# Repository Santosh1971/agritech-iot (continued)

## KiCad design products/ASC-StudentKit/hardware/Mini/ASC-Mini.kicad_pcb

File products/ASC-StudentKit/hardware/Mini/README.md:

# ASC Mini rev A: schematic

The Mini carrier board for the ASC Student Kit. It is a half board, **97.4 × 47.0 mm**, held by **3 × M3** on the box's upper three bosses. Two Minis fit on one 100 × 100 mm panel (kit architecture §8).

## Status

| Item | State |
|---|---|
| Schematic | **First draft, generated.** 92 parts, 55 nets. `tools/check_design.py` and `tools/check_sheet.py` pass. **KiCad's ERC has not been run yet** (no KiCad 9 in the build container). Run it on the Mac first. |
| Pin map | Matches `../pinmap.json` (board `mini`), checked by `tools/check_design.py` |
| Footprints | 0402 resistors and small capacitors. J3 (the tester's pins) is a row of SMD pads on the back under the module, not fitted (DNP). The RTC cell holder is the flat Keystone 3034 on the back. 25 come from the KiCad 9.0.9 library. The HF46F relay footprint is our own (`ASC.pretty`), drawn from the Hongfa datasheet's PCB layout; check it against a real relay before ordering. The Grove socket uses a JST-PH 4-pin footprint as a stand-in; swap it for the HY2.0-4P part at layout. |
| PCB | **Routed, 2 layers, 1.6 mm.** 97.4 × 47.0 mm, 3 × M3. 1581 tracks (narrowest 0.15 mm), 287 vias (0.55 / 0.3 mm), clearance 0.15 mm. GND is joined by tracks as well as the pours on both layers. All checks below pass. **KiCad's zone fill and DRC have not been run yet** (no KiCad in the build container); run them on the Mac before ordering. |

## What is on it

| Block | Parts | Notes |
|---|---|---|
| 12 V input | J1 2-way 5.08 mm terminal, D1 SS34 (reverse polarity), D2 SMAJ26A (TVS), C1–C3 | **9–24 V in, 24 V maximum.** A terminal rather than a barrel jack, so the cable comes through a gland. |
| 12 V → 5 V | U2 TPS54202 buck (28 V max, 2 A), L1 10 µH, R1/R2 set **5.3 V**, D3 SS34 | The diode drop leaves about 5.0 V on +5V |
| USB-C | J2, R3/R4 5.1 k CC pull-downs, F1 0.5 A PTC, D4 SS34, U3 USBLC6-2SC6 ESD | Flashing and the console over native USB (GPIO19/20); also powers the board on a desk. D3 and D4 OR the two 5 V sources. |
| 5 V → 3.3 V | U4 AP7361C-33E (1 A LDO) | ESP32-S3 WiFi peaks of ≈350 mA, plus the RTC and the 3.3 V sensors |
| MCU | U1 ESP32-S3-MINI-1-**N8** | EN: R8/C14 plus a **RESET** button. GPIO0: R9 plus the **PAIR/BOOT** button. |
| Board ID | R10 30 k / R11 10 k = 0.25 × 3V3 on GPIO11 | The firmware reads this as "mini" |
| 12 V sense | R5 100 k / R6 10 k on GPIO10 | 24 V reads 2.18 V; 0 V means USB power only |
| RTC | U5 DS3231MZ+ (SOIC-8), BT1 CR2032 **on the back**, INT/SQW → GPIO16 | Internal I²C bus (GPIO12/13, 4.7 k pull-ups) |
| Sensor ports S1–S4 | J4–J7 JST-XH 4-pin: 1 GND · 2 3V3 · 3 5V · 4 SIG | SIG: 470 Ω in series, BAT54S clamps to 3V3 and GND, so a 5 V digital signal such as a flow sensor is safe. Port supplies fused: F2 0.5 A (5 V), F3 0.2 A (3V3). |
| I2C-1 student port | J8 Grove pinout: 1 SCL · 2 SDA · 3 3V3 · 4 GND | Its own bus (GPIO14/15), 4.7 k pull-ups |
| Relays OUT1/OUT2 | K1/K2 **Hongfa HF46F/005-HS1** (1 Form A, 5 A, 20.5 × 7.2 mm, 40 mA coil), Q2/Q3 AO3400A, D12/D13 flyback, J9/J10 2-way terminals (COM · NO) | GPIO35/36, gate pull-downs so the relays stay off through reset. Normally open only, which is all the rules use. **LOW VOLTAGE ONLY** on the silkscreen. |
| Buzzer | BZ1 5 V active 12 mm, Q1 AO3400A, D7 | GPIO46 is a strapping pin: R14 holds it low at reset |
| LEDs, seen through the clear lid | D5 **PWR**, D6 **STATUS** (GPIO48), D14 **OUT1**, D15 **OUT2** (on the relay coils, so they need no GPIO) | Each LED's name goes on the silkscreen (the `Silk` field on each part) |
| Test header | J3 1.27 mm × 8: 3V3, GND, EN, PAIR, D−, D+, TX, RX | The production tester's pogo pins, the same set as AWD1 |
| Mounting | H1–H3 M3 | Positions in `design.py` |

## Decided

- **Relays:** Hongfa HF46F (2026-10-08). It replaces the SRD and saves about 300 mm² of board.
- **Input:** 24 V maximum (2026-10-08). The TPS54202 (28 V) and the SMAJ26A suit that.
- **No OLED** in the kits (2026-10-08). The phone app is the screen, and the LEDs show through the clear lid.

## Please review

1. **Connector row.** The bottom edge has room for about 78 mm of connectors between the screw bosses. The three terminals (OUT1, OUT2, 12 V IN) need about 31 mm. The four XH ports and the Grove socket need about 58 mm more. Proposal: terminals along the bottom edge, and the XH and Grove sockets (vertical) in a second row just above them, with cables running down past the edge. USB-C goes on a side edge.
2. **HF46F footprint.** Print the footprint at 1:1 and push a real relay's pins through the paper before the first order.

## On the Mac, before ordering

1. Open `ASC-Mini.kicad_pro` in KiCad 9.
2. In the PCB editor press **B** to fill the zones (GND on both layers).
3. Run **Inspect → Design Rules Checker**. Expect nothing but silkscreen cosmetics. The USB-C footprint's own pads sit exactly 0.2 mm apart, which is fine under the 0.15 mm rule.
4. Check the HF46F relay footprint against a real relay (print 1:1).
5. Plot gerbers and drill files, or use the JLC plugin. Order 2 boards per 100 × 100 mm panel (architecture §8).

## Regenerate

```bash
cd products/ASC-StudentKit/hardware/Mini
python3 tools/gen_sch.py          # ASC-Mini.kicad_sch and tools/netlist.json
python3 tools/check_design.py     # pins vs pinmap.json, nets, power, strapping pins
python3 tools/check_sheet.py      # no accidental connections or overlaps on the sheet
python3 tools/gen_pcb.py          # ASC-Mini.kicad_pcb: outline, holes, placement, zones, labels (unrouted)
```

The board is routed by these steps. Freerouting 2.5.0 comes from Maven Central and needs Java 25:

```bash
export FREEROUTING_JAR=…/freerouting-2.5.0-executable.jar JAVA=…/java-25/bin/java
ROUTE_STAGE=signals POWER_W=0.45 SUPPLY_W=0.3 CLEARANCE=0.19 VIA_D=0.55 python3 tools/route.py   # every net but GND
python3 tools/patch_route.py                              # A* grid router with rip-up: whatever Freerouting left open
ROUTE_STAGE=gnd python3 tools/route.py                    # GND as tracks around the signals
PATCH_FINE=1 PATCH_CLR=0.16 python3 tools/patch_route.py GND
python3 tools/nudge_vias.py                               # move any via the grid left too close
```

Freerouting's result changes a lot with small inputs. The `ROUTE_TAG` and `ROUTE_ONLY` options run several variants side by side, so the best one can be imported. After a part moves, `tools/carry_routing.py OLD.kicad_pcb` keeps the existing routing except near the moved part, and `patch_route.py` reconnects the rest.

Checks, all passing on the committed board:

```bash
python3 tools/check_connect.py --include-gnd   # every net joined by copper (the module's GND pads are tied inside it)
python3 tools/check_clearance.py               # tracks, vias and pads of different nets ≥ 0.15 mm; edge; holes
python3 tools/check_board.py                   # pads clear of the edge and the screw heads
python3 tools/check_pour.py                    # GND is one piece; no dead pour patches or vias
```

`gen_sch.py` reads KiCad's symbol libraries from `KICAD_SYMBOL_DIR`. The default is KiCad 9 on macOS (`/Applications/KiCad/KiCad.app/Contents/SharedSupport/symbols`).

Then open `ASC-Mini.kicad_pro` in KiCad 9 and run **Inspect → Electrical Rules Checker**.

Edit `tools/design.py` and regenerate, rather than editing the schematic by hand, until the board layout starts. After that, switch to editing in KiCad, as AWD1 did.

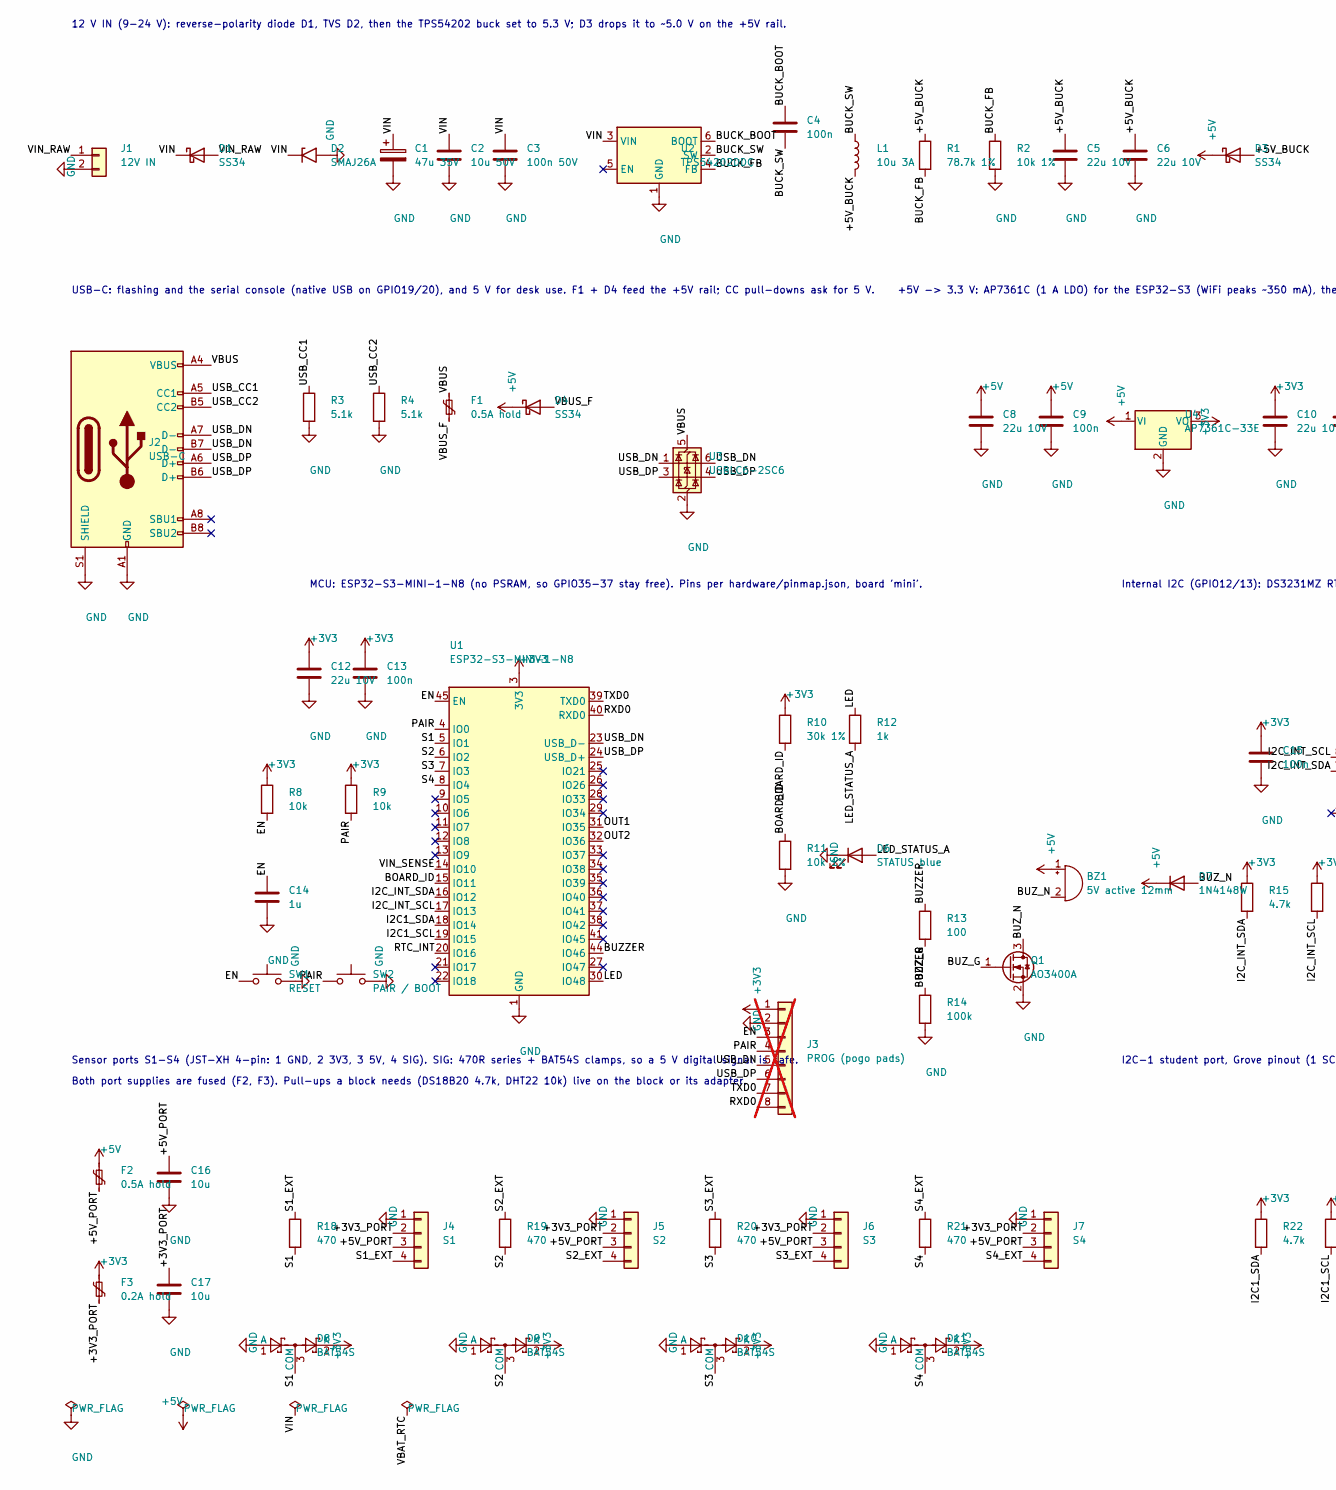
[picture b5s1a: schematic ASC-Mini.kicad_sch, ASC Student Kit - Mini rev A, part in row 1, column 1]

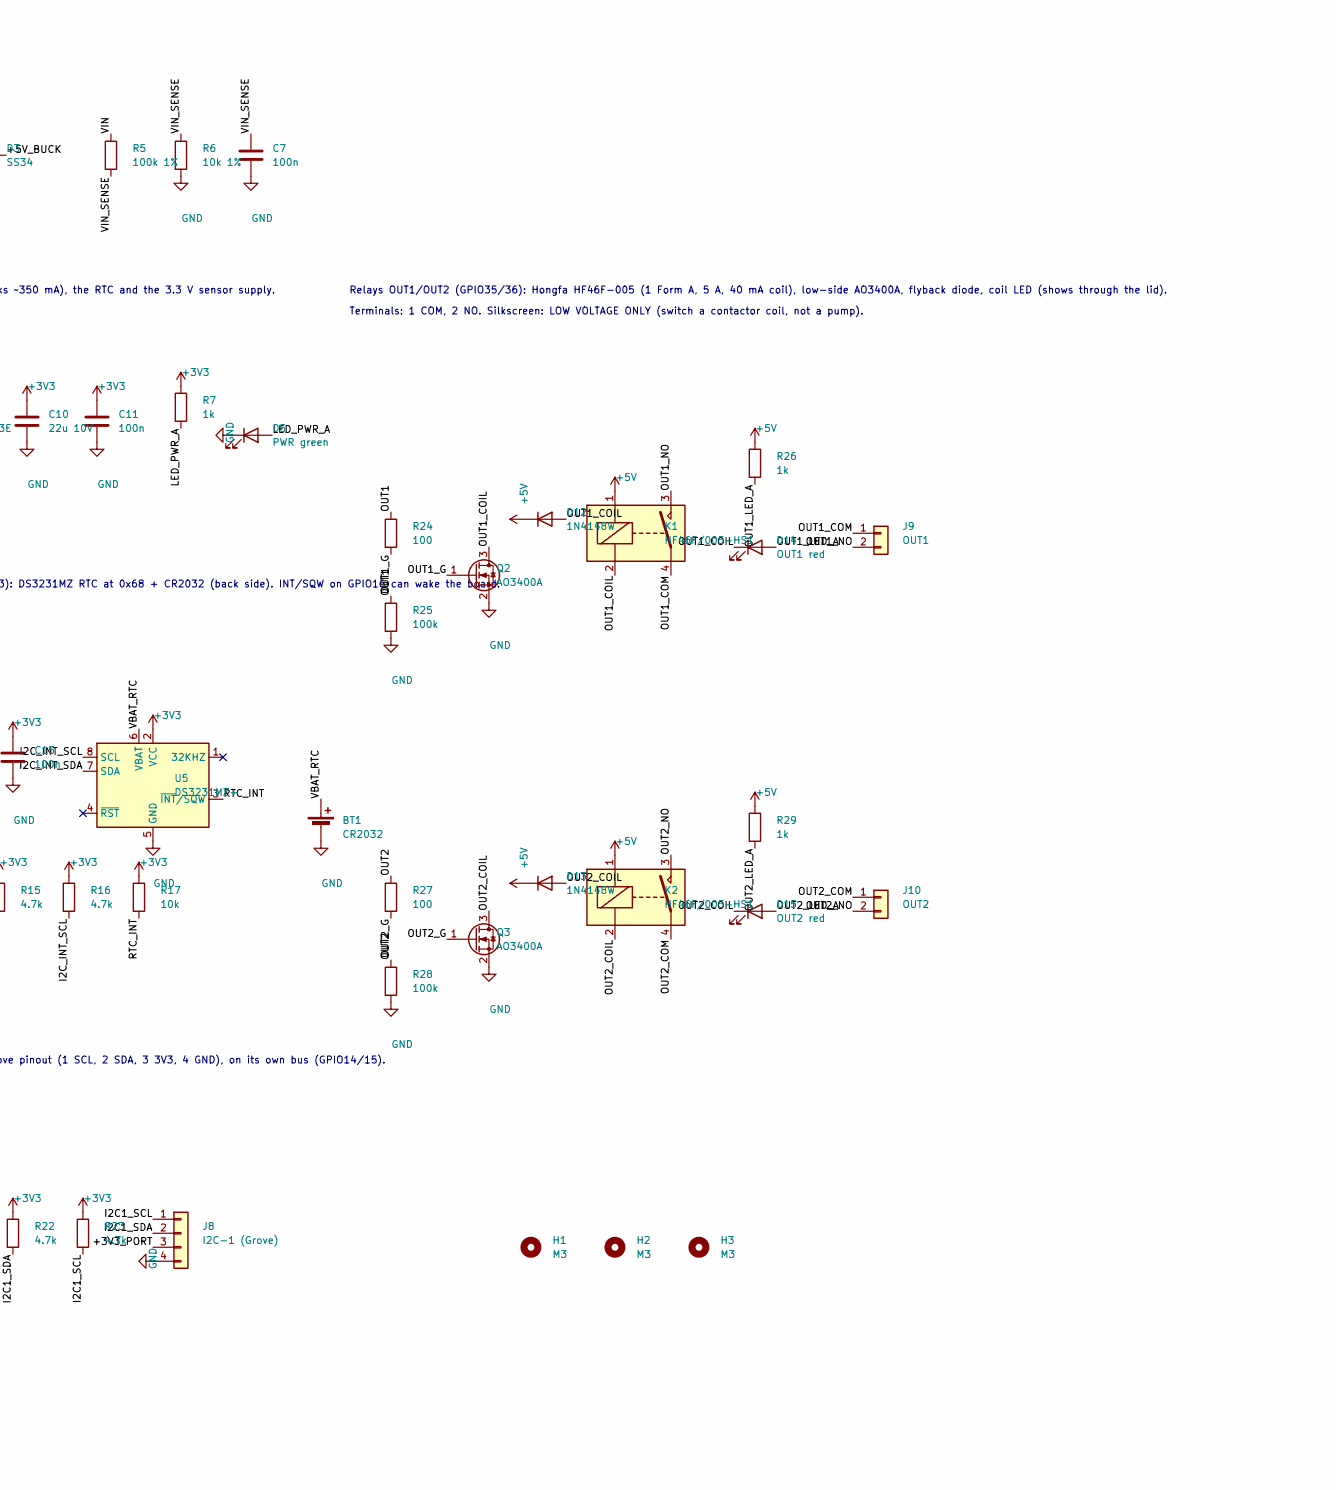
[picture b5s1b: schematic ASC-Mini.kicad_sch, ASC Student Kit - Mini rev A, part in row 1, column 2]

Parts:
BT1: CR2032; BatteryHolder_Keystone_3034_1x20mm
BZ1: 5V active 12mm; Buzzer_12x9.5RM7.6
C1: 47u 35V; CP_Elec_6.3x5.4
C2: 10u 50V; C_1206_3216Metric
C3: 100n 50V; C_0402_1005Metric
C4, C7, C9, C11, C13, C15: 100n; C_0402_1005Metric
C5, C6, C8, C10, C12: 22u 10V; C_1206_3216Metric
C14: 1u; C_0402_1005Metric
C16, C17: 10u; C_0805_2012Metric
D1, D3, D4: SS34; D_SMA
D2: SMAJ26A; D_SMA
D5: PWR green; LED_0805_2012Metric
D6: STATUS blue; LED_0805_2012Metric
D7, D12, D13: 1N4148W; D_SOD-123
D8, D9, D10, D11: BAT54S; SOT-23
D14: OUT1 red; LED_0805_2012Metric
D15: OUT2 red; LED_0805_2012Metric
F1, F2: 0.5A hold; Fuse_1206_3216Metric
F3: 0.2A hold; Fuse_1206_3216Metric
H1, H2, H3: M3; MountingHole_3.2mm_M3
J1: 12V IN; PhoenixContact_MSTBA_2,5_2-G-5,08_1x02_P5.08mm_Horizontal
J2: USB-C; USB_C_Receptacle_HRO_TYPE-C-31-M-12
J3: PROG (pogo pads); PinHeader_1x08_P1.27mm_Vertical_SMD_Pin1Left; not fitted
J4: S1; JST_XH_B4B-XH-A_1x04_P2.50mm_Vertical
J5: S2; JST_XH_B4B-XH-A_1x04_P2.50mm_Vertical
J6: S3; JST_XH_B4B-XH-A_1x04_P2.50mm_Vertical
J7: S4; JST_XH_B4B-XH-A_1x04_P2.50mm_Vertical
J8: I2C-1 (Grove); JST_PH_B4B-PH-K_1x04_P2.00mm_Vertical
J9: OUT1; PhoenixContact_MSTBA_2,5_2-G-5,08_1x02_P5.08mm_Horizontal
J10: OUT2; PhoenixContact_MSTBA_2,5_2-G-5,08_1x02_P5.08mm_Horizontal
K1, K2: HF46F/005-HS1; Relay_SPST_Hongfa_HF46F
L1: 10u 3A; L_6.3x6.3_H3
Q1, Q2, Q3: AO3400A; SOT-23
R1: 78.7k 1%; R_0402_1005Metric
R2, R6, R11: 10k 1%; R_0402_1005Metric
R3, R4: 5.1k; R_0402_1005Metric
R5: 100k 1%; R_0402_1005Metric
R7, R12, R26, R29: 1k; R_0402_1005Metric
R8, R9, R17: 10k; R_0402_1005Metric
R10: 30k 1%; R_0402_1005Metric
R13, R24, R27: 100; R_0402_1005Metric
R14, R25, R28: 100k; R_0402_1005Metric
R15, R16, R22, R23: 4.7k; R_0402_1005Metric
R18, R19, R20, R21: 470; R_0402_1005Metric
SW1: RESET; SW_SPST_TL3342
SW2: PAIR / BOOT; SW_SPST_TL3342
U1: ESP32-S3-MINI-1-N8; ESP32-S2-MINI-1
U2: TPS54202DDC; SOT-23-6
U3: USBLC6-2SC6; SOT-23-6
U4: AP7361C-33E; SOT-223-3_TabPin2
U5: DS3231MZ+; SOIC-8_3.9x4.9mm_P1.27mm

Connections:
+3V3: C10.1, C11.1, C12.1, C13.1, C15.1, D8.2 (K), D9.2 (K), D10.2 (K), D11.2 (K), F3.1, J3.1, R7.1, R8.1, R9.1, R10.1, R15.1, R16.1, R17.1, R22.1, R23.1, U1.3 (3V3), U4.3 (VO), U5.2 (VCC)
+5V: BZ1.1 (+), C8.1, C9.1, D3.1 (K), D4.1 (K), D7.1 (K), D12.1 (K), D13.1 (K), F2.1, K1.1, K2.1, R26.1, R29.1, U4.1 (VI)
/+3V3_PORT: C17.1, F3.2, J4.2, J5.2, J6.2, J7.2, J8.3
/+5V_BUCK: C5.1, C6.1, D3.2 (A), L1.2, R1.1
/+5V_PORT: C16.1, F2.2, J4.3, J5.3, J6.3, J7.3
/BOARD_ID: R10.2, R11.1, U1.15 (IO11)
/BUCK_BOOT: C4.1, U2.6 (BOOT)
/BUCK_FB: R1.2, R2.1, U2.4 (FB)
/BUCK_SW: C4.2, L1.1, U2.2 (SW)
/BUZZER: R13.1, R14.1, U1.44 (IO46)
/BUZ_G: Q1.1 (G), R13.2
/BUZ_N: BZ1.2 (-), D7.2 (A), Q1.3 (D)
/EN: C14.1, J3.3, R8.2, SW1.1, U1.45 (EN)
/I2C1_SCL: J8.1, R23.2, U1.19 (IO15)
/I2C1_SDA: J8.2, R22.2, U1.18 (IO14)
/I2C_INT_SCL: R16.2, U1.17 (IO13), U5.8 (SCL)
/I2C_INT_SDA: R15.2, U1.16 (IO12), U5.7 (SDA)
/LED: R12.1, U1.30 (IO48)
/LED_PWR_A: D5.2 (A), R7.2
/LED_STATUS_A: D6.2 (A), R12.2
/OUT1: R24.1, R25.1, U1.31 (IO35)
/OUT1_COIL: D12.2 (A), D14.1 (K), K1.2, Q2.3 (D)
/OUT1_COM: J9.1, K1.4
/OUT1_G: Q2.1 (G), R24.2
/OUT1_LED_A: D14.2 (A), R26.2
/OUT1_NO: J9.2, K1.3
/OUT2: R27.1, R28.1, U1.32 (IO36)
/OUT2_COIL: D13.2 (A), D15.1 (K), K2.2, Q3.3 (D)
/OUT2_COM: J10.1, K2.4
/OUT2_G: Q3.1 (G), R27.2
/OUT2_LED_A: D15.2 (A), R29.2
/OUT2_NO: J10.2, K2.3
/PAIR: J3.4, R9.2, SW2.1, U1.4 (IO0)
/RTC_INT: R17.2, U1.20 (IO16), U5.3 (~INT/SQW)
/RXD0: J3.8, U1.40 (RXD0)
/S1: D8.3 (COM), R18.2, U1.5 (IO1)
/S1_EXT: J4.4, R18.1
/S2: D9.3 (COM), R19.2, U1.6 (IO2)
/S2_EXT: J5.4, R19.1
/S3: D10.3 (COM), R20.2, U1.7 (IO3)
/S3_EXT: J6.4, R20.1
/S4: D11.3 (COM), R21.2, U1.8 (IO4)
/S4_EXT: J7.4, R21.1
/TXD0: J3.7, U1.39 (TXD0)
/USB_CC1: J2.A5 (CC1), R3.1
/USB_CC2: J2.B5 (CC2), R4.1
/USB_DN: J2.A7 (D-), J2.B7 (D-), J3.5, U1.23 (USB_D-), U3.1 (I/O1), U3.6 (I/O1)
/USB_DP: J2.A6 (D+), J2.B6 (D+), J3.6, U1.24 (USB_D+), U3.3 (I/O2), U3.4 (I/O2)
/VBAT_RTC: BT1.1 (+), U5.6 (VBAT)
/VBUS: F1.1, J2.A4 (VBUS), J2.A9 (VBUS), J2.B4 (VBUS), J2.B9 (VBUS), U3.5 (VBUS)
/VBUS_F: D4.2 (A), F1.2
/VIN: C1.1, C2.1, C3.1, D1.1 (K), D2.1 (A1), R5.1, U2.3 (VIN)
/VIN_RAW: D1.2 (A), J1.1
/VIN_SENSE: C7.1, R5.2, R6.1, U1.14 (IO10)
GND: BT1.2 (-), C1.2, C2.2, C3.2, C5.2, C6.2, C7.2, C8.2, C9.2, C10.2, C11.2, C12.2, C13.2, C14.2, C15.2, C16.2, C17.2, D2.2 (A2), D5.1 (K), D6.1 (K), D8.1 (A), D9.1 (A), D10.1 (A), D11.1 (A), J1.2, J2.A1 (GND), J2.A12 (GND), J2.B1 (GND), J2.B12 (GND), J2.S1 (SHIELD), J3.2, J4.1, J5.1, J6.1, J7.1, J8.4, Q1.2 (S), Q2.2 (S), Q3.2 (S), R2.2, R3.2, R4.2, R6.2, R11.2, R14.2, R25.2, R28.2, SW1.2, SW2.2, U1.1 (GND), U1.2 (GND), U1.42 (GND), U1.43 (GND), U1.46 (GND), U1.47 (GND), U1.48 (GND), U1.49 (GND), U1.50 (GND), U1.51 (GND), U1.52 (GND), U1.53 (GND), U1.54 (GND), U1.55 (GND), U1.56 (GND), U1.57 (GND), U1.58 (GND), U1.59 (GND), U1.60 (GND), U1.61 (GND), U1.62 (GND), U1.63 (GND), U1.64 (GND), U1.65 (GND), U2.1 (GND), U3.2 (GND), U4.2 (GND), U5.5 (GND)

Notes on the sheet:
12 V IN (9-24 V): reverse-polarity diode D1, TVS D2, then the TPS54202 buck set to 5.3 V; D3 drops it to ~5.0 V on the +5V rail.
USB-C: flashing and the serial console (native USB on GPIO19/20), and 5 V for desk use. F1 + D4 feed the +5V rail; CC pull-downs ask for 5 V.
+5V -> 3.3 V: AP7361C (1 A LDO) for the ESP32-S3 (WiFi peaks ~350 mA), the RTC and the 3.3 V sensor supply.
MCU: ESP32-S3-MINI-1-N8 (no PSRAM, so GPIO35-37 stay free). Pins per hardware/pinmap.json, board 'mini'.
Internal I2C (GPIO12/13): DS3231MZ RTC at 0x68 + CR2032 (back side). INT/SQW on GPIO16 can wake the board.
Sensor ports S1-S4 (JST-XH 4-pin: 1 GND, 2 3V3, 3 5V, 4 SIG). SIG: 470R series + BAT54S clamps, so a 5 V digital signal is safe.
Both port supplies are fused (F2, F3). Pull-ups a block needs (DS18B20 4.7k, DHT22 10k) live on the block or its adapter.
I2C-1 student port, Grove pinout (1 SCL, 2 SDA, 3 3V3, 4 GND), on its own bus (GPIO14/15).
Relays OUT1/OUT2 (GPIO35/36): Hongfa HF46F-005 (1 Form A, 5 A, 40 mA coil), low-side AO3400A, flyback diode, coil LED (shows through the lid).
Terminals: 1 COM, 2 NO. Silkscreen: LOW VOLTAGE ONLY (switch a contactor coil, not a pump).

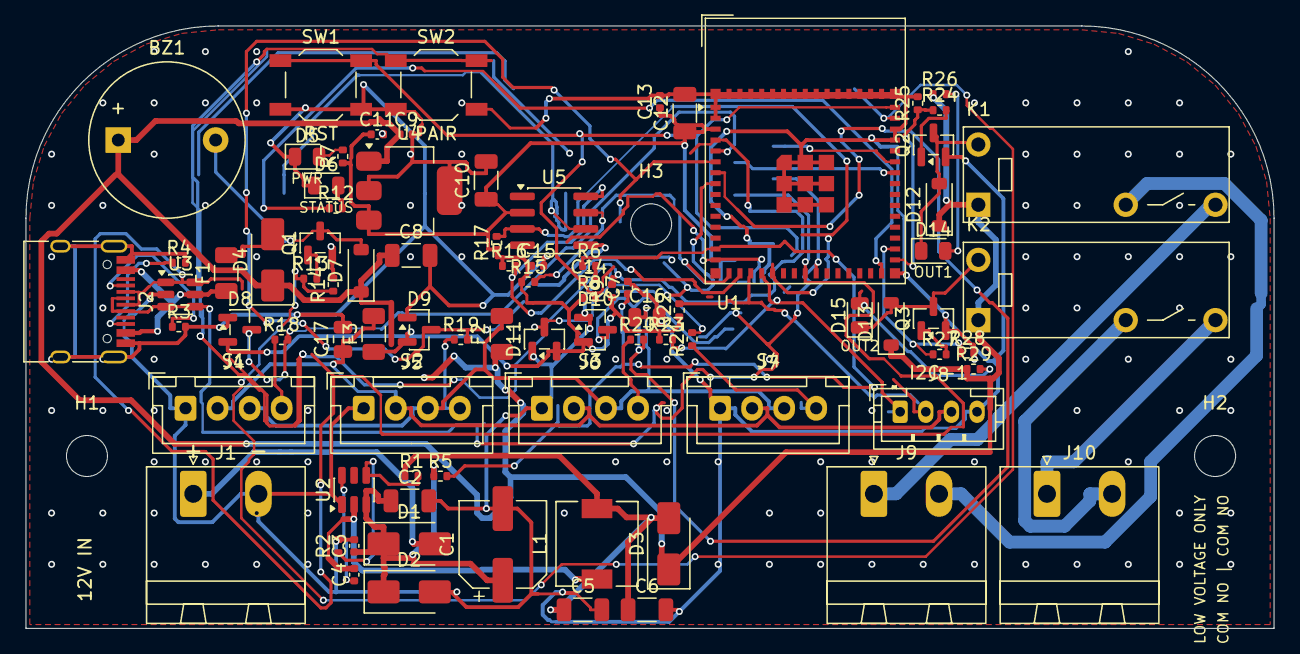
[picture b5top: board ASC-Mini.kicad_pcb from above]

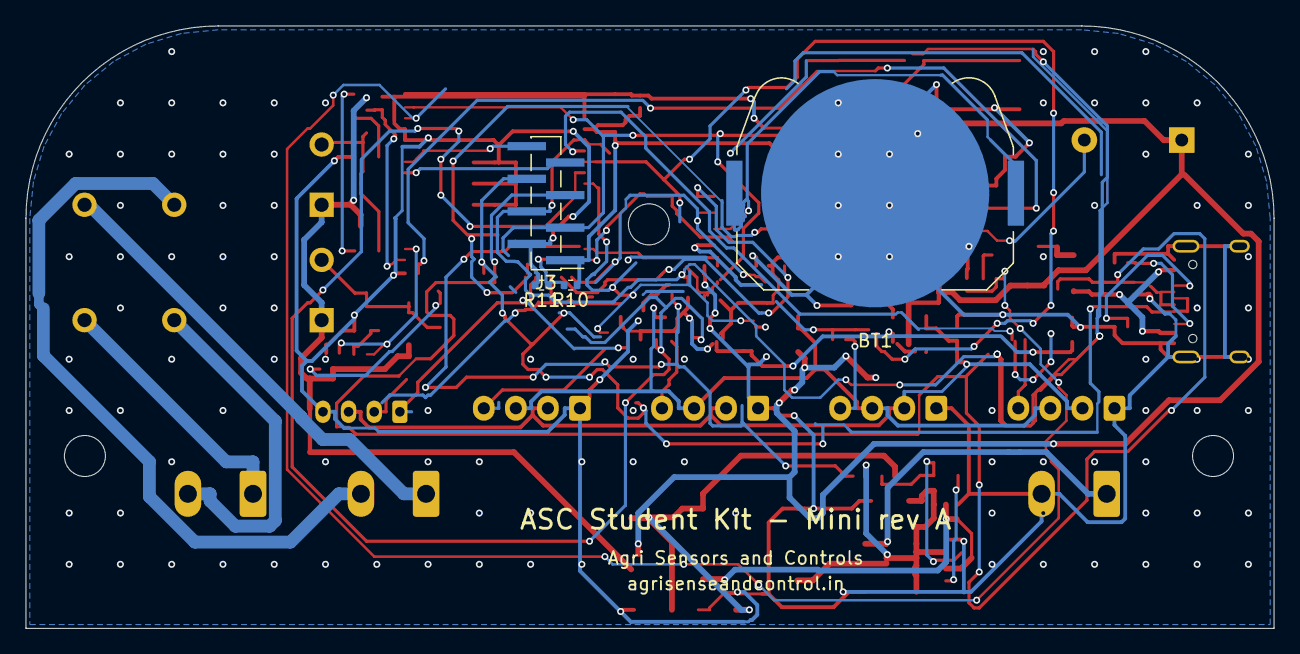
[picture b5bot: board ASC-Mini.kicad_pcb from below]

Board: 2 copper layers, 97.4 x 47.0 mm, 92 parts (4 on the bottom side), 55 nets.

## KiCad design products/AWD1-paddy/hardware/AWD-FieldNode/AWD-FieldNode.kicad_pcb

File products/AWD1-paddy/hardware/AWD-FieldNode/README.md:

# AWD field node v0.1: segmented capacitive level strip

This board is the paddy AWD (alternate wetting and drying) field node. It is a T-shaped, 4-layer PCB.

- **Head:** 40 × 60 mm, inside a sealed 50 mm PVC end cap. It carries an ESP32-S3-MINI-1, an ISC-SX1262-B LoRa module (the same module and pin map as WPC), a LiFePO4 14500 cell and an SMA connector.
- **Strip:** 10 × 300 mm, pushed into the AWD tube.
  - 12 sensing pads, 8 × 18 mm on a 20 mm pitch, covering +7 to −17 cm.
  - One dry reference pad.
  - One GND water-return pad.

The node reports to a WPC-style Master over LoRa at 866 MHz.

## Status

| Item | State |
|---|---|
| Schematic | **v0.2 (2026-10-11): field charging added**, the same block as TH2 (see *v0.2 power* below). 66 parts, ERC reports 0 violations. |
| PCB ↔ schematic | **Out of date since v0.2.** The 51 existing footprints are still linked: `gen_sch.py` now keeps symbol UUIDs. The 15 new parts (U3, U4, U5, F1, J4, D2, D3, R8–R13, C8, C9) must be added with *Update PCB from Schematic*, then placed and routed on the head. TP1 is renamed from T14 to VBUS_DET. |
| Outline, stack-up, zones | Done. Board is 4 layers: F pads / In1 GND (hatched 25 % under the pads) / In2 sense lanes + GND / B GND. |
| Strip routing | **Done.** Each pad → via → In2.Cu lane (0.15 mm, 0.6 mm pitch) → 45° fan-out → RS series resistor. |
| Head placement | Placed next to the pins each part serves. J3 (battery JST) is on the back, under the SX1262. |
| Head routing | **Done** by Freerouting 1.9.0 (passes in `route/`) on F.Cu and In2.Cu, with GND stitching vias added by `tools/stitch.py`. Hand-routed nets: R4's +3V3 (via → B.Cu → J2 pin 1); the SX1262 VDD feed (B.Cu at x = 107.4 mm), which clears the straight 50 Ω antenna line. |
| Remaining DRC | **U1 pad 63** (an ESP32 corner GND pad) sits in a small F.Cu GND island. The touch fan-out fills that corner, so no via fits. It is harmless because the module ties its GND pads together internally. **J1** is an edge-launch SMA and touches the edge on purpose; check its seating against the Amphenol 132289 datasheet. The rest are silkscreen cosmetics and three single-spoke thermals. |

## Pin map (ESP32-S3)

| Function | GPIO |
|---|---|
| Touch T1–T12 → pads P1–P12 | IO1–IO12 |
| Touch T13 → REF pad | IO13 |
| VBUS_DET (charger present, deep-sleep wake), to TP1 | IO14 |
| VBAT_ADC (ADC2_CH4) / VBAT_EN | IO15 / IO16 |
| LoRa DIO1 / BUSY / RST | IO17 / IO18 / IO21 |
| LoRa NSS / SCK / MOSI / MISO | IO39 / IO40 / IO41 / IO42 |
| LED | IO38 |
| PAIR/BOOT button | IO0 |
| USB D−/D+ and UART0 | J2 (1.27 mm pogo/header) |

## v0.2 power: charging in the field through a magnetic socket

v0.1 put the 14500 straight onto the 3V3 rail with no charger, so the box had to be opened to charge the cell. v0.2 adds the same charging block as TH2:

```
J4 magnetic socket (VBUS, D-, D+, GND) -> F1 0.5 A polyfuse -> VBUS -> U3 CN3058E (0.31 A, 3.6 V CV) -> VBAT
J3 14500 -> Q1 reverse protection -> VBAT -> U4 RT9080-33 (2 uA Iq) -> +3V3
```

- **The LDO is now required:** while charging, VBAT sits at 3.6 V, which is the ESP32-S3's absolute maximum.
- **Battery sense:** R4 now measures **VBAT** (before the LDO), not +3V3.
- **USB:** J4's D−/D+ join the native-USB lines already on J2, through U5 (USBLC6 ESD protection). The node can be flashed through the magnetic cable without opening the box.
- **Charge LEDs:** D2 red (charging) and D3 green (full) run off VBUS. Place them under, or next to, the front-shell light window.
- **Charger detect:** VBUS_DET (R12/R13 divider to IO14, an RTC GPIO) wakes the S3 when the cable is clipped on.
- **Enclosure:** the magnetic socket needs its own wall hole, because the side hole is used by the SMA. That waits until the socket's flange size is known (ElectronifyIndia 4-pin flanged for prototypes, HytePro M826 waterproof for production). It goes in the shared AWD/TH shell.

## AWD thresholds

| Action | Condition |
|---|---|
| Pump OFF (+5 cm) | P2 wet |
| Pump ON (−15 cm) | P11 dry |
| SOIL line (0 cm) | Printed on both faces as the installation depth mark |

## Regenerate

The files are generated from `tools/design.py`, which defines the parts, nets and geometry.

```bash
cd products/AWD1-paddy/hardware/AWD-FieldNode
python3 tools/gen_sch.py      # schematic, AWD.kicad_sym, tools/netlist.json
python3 tools/gen_fp.py       # AWD.pretty pad footprints
/Applications/KiCad/KiCad.app/Contents/Frameworks/Python.framework/Versions/Current/bin/python3 tools/gen_pcb.py
```

**Warning:** `gen_pcb.py` rebuilds the board from scratch and **throws away the head routing**. Never run it again. `gen_sch.py` is safe: since v0.2 it reuses the existing schematic's root and symbol UUIDs, so the routed PCB stays linked. After a regenerate, run *Update PCB from Schematic* in KiCad to pull in new parts.

### Re-routing the head and watching it

To watch the autorouter work:

1. Unlock the strip tracks if you need to move them; leave them locked otherwise.
2. Remove the `GND_top_head` and `GND_in2` zones.
3. Run *File → Export → Specctra DSN*.
4. In the `.dsn` file, change `In1.Cu` (and optionally `B.Cu`) to `(type power)`.
5. Run:

```bash
java -jar ~/Applications/freerouting/freerouting-1.9.0.jar -de route/AWD-FieldNode.dsn
```

6. Press **Autorouter** in the Freerouting window to watch it route.
7. Save the session, then run *File → Import → Specctra Session* in KiCad.
8. Refill the zones (B).

## Fab notes

- **Order with JLCPCB stack-up JLC04161H-7628** (L1–L2 prepreg 0.21 mm, εr ≈ 4.4). The antenna feed (`/RF_ANT`, SX1262 pad 1 → J1) is a straight 10.9 mm, 0.36 mm trace on F.Cu over the In1 GND plane: about 50 Ω. `AWD-FieldNode.kicad_dru` keeps the F.Cu pour 0.5 mm away from it. To hold ±10 %, tick impedance control.
- `fab/` holds gerbers + drills (`AWD-FieldNode-gerbers.zip`), BOM and CPL. These were exported with kicad-cli; regenerate them after any board change.

- 4 layers, 1.6 mm FR4, ENIG finish, solder mask on both sides, vias tented.
- The pads have **no mask opening**. Below the neck the strip carries no exposed copper.
- After assembly, dip-coat the strip in 2-part epoxy or PU, 100–200 µm thick, and seal the routed edges.

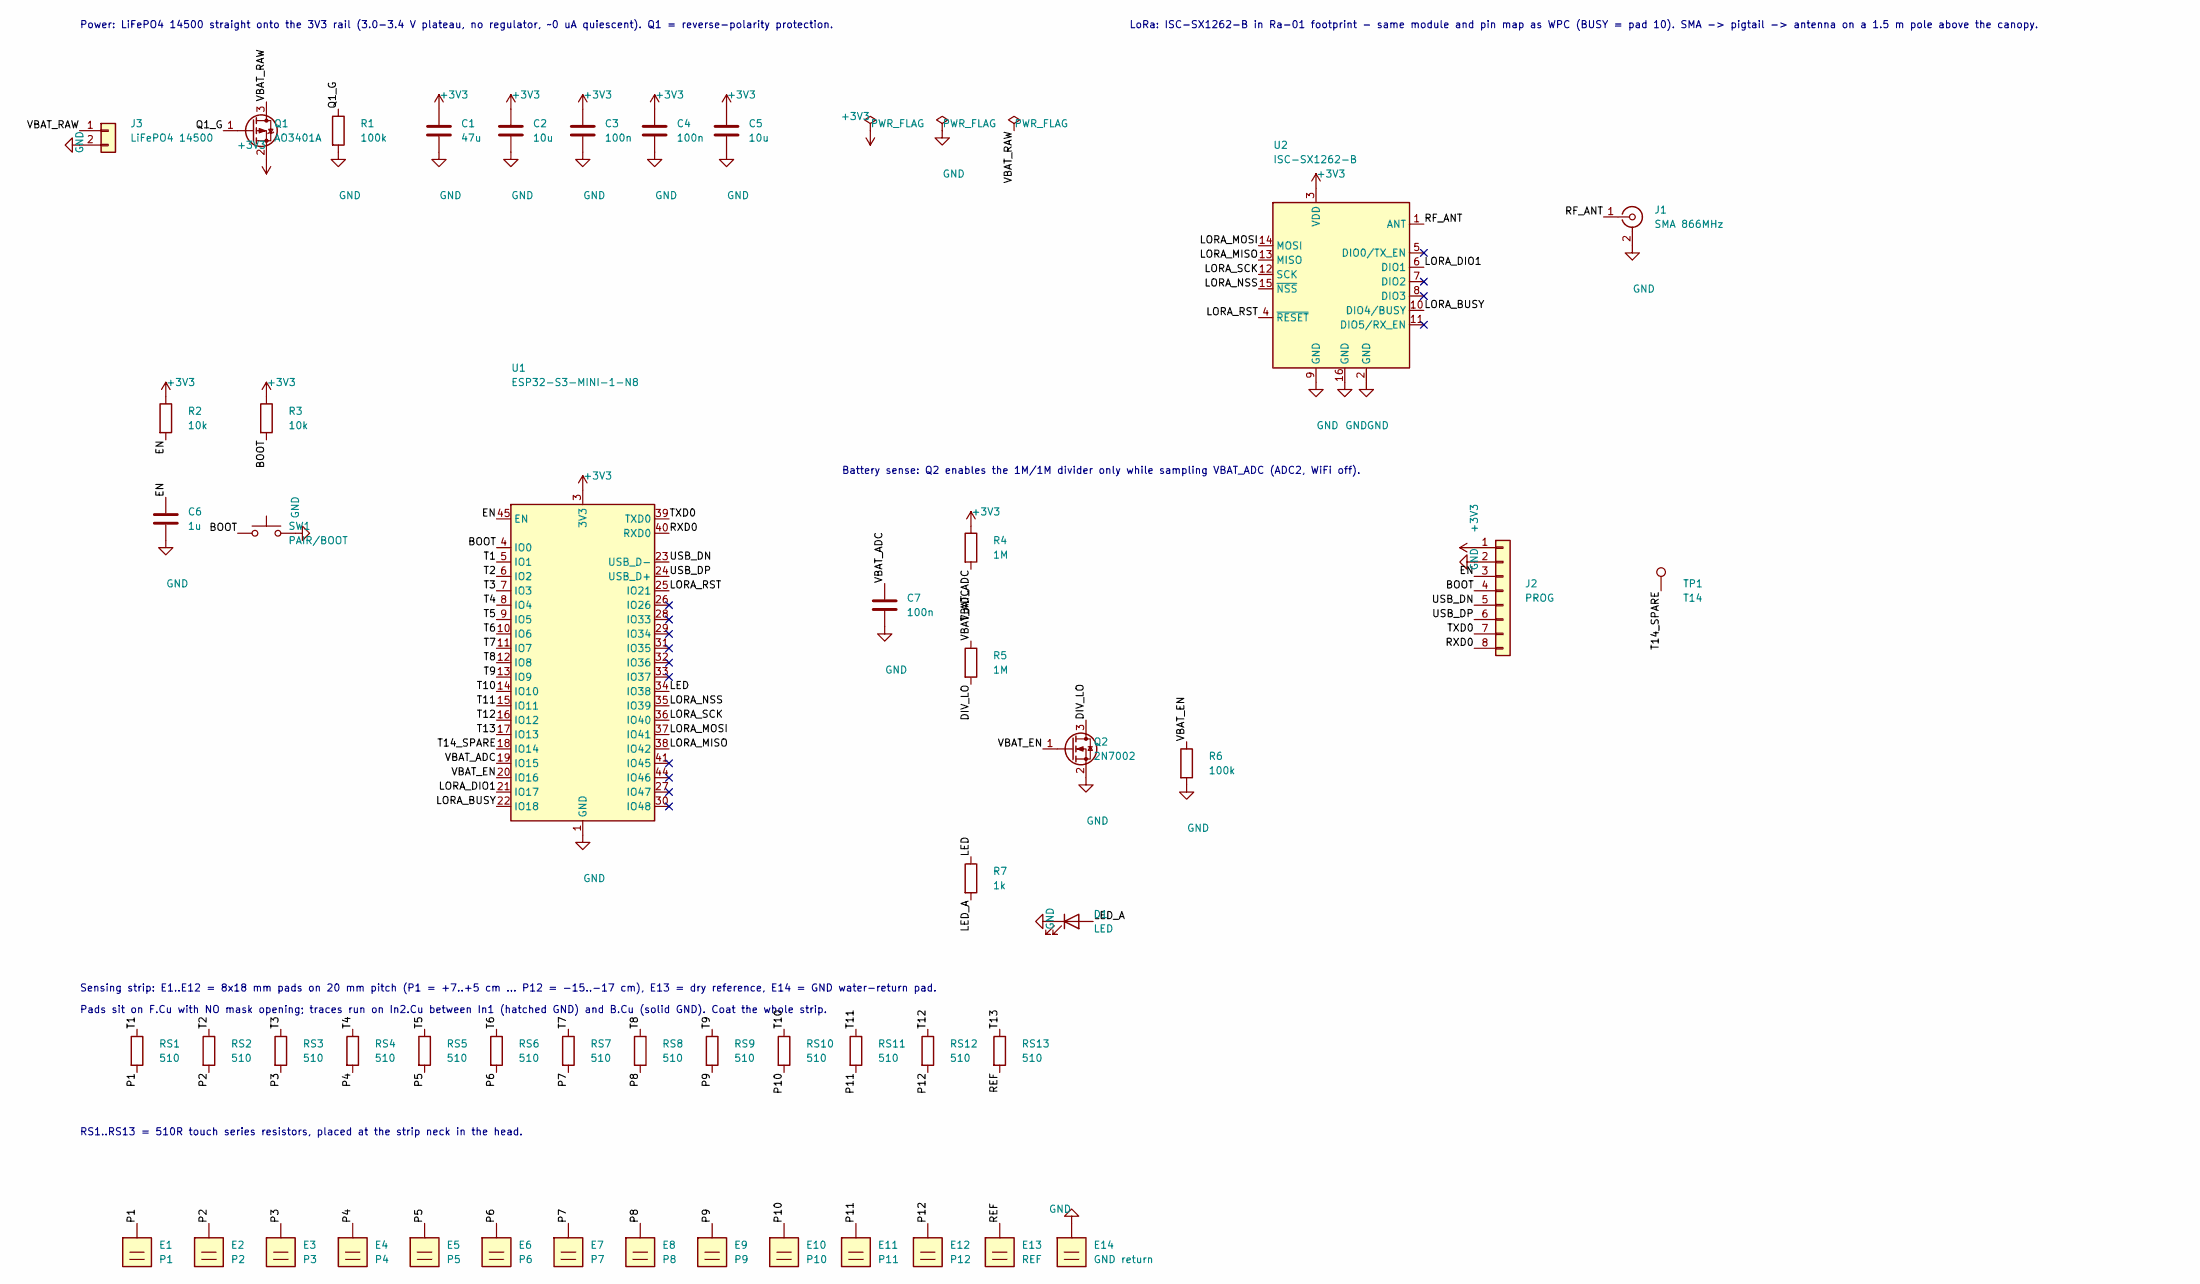
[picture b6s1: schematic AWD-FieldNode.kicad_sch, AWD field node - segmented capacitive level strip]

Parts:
C1: 47u; C_1206_3216Metric
C2, C5: 10u; C_0805_2012Metric
C3, C4, C7: 100n; C_0603_1608Metric
C6: 1u; C_0603_1608Metric
D1: LED; LED_0603_1608Metric
E1: P1; SensePad_8x18mm
E2: P2; SensePad_8x18mm
E3: P3; SensePad_8x18mm
E4: P4; SensePad_8x18mm
E5: P5; SensePad_8x18mm
E6: P6; SensePad_8x18mm
E7: P7; SensePad_8x18mm
E8: P8; SensePad_8x18mm
E9: P9; SensePad_8x18mm
E10: P10; SensePad_8x18mm
E11: P11; SensePad_8x18mm
E12: P12; SensePad_8x18mm
E13: REF; SensePad_8x12mm
E14: GND return; ReturnPad_8x20mm
J1: SMA 866MHz; SMA_Amphenol_132289_EdgeMount
J2: PROG; PinHeader_1x08_P1.27mm_Vertical
J3: LiFePO4 14500; JST_PH_S2B-PH-SM4-TB_1x02-1MP_P2.00mm_Horizontal
Q1: AO3401A; SOT-23
Q2: 2N7002; SOT-23
R1, R6: 100k; R_0603_1608Metric
R2, R3: 10k; R_0603_1608Metric
R4, R5: 1M; R_0603_1608Metric
R7: 1k; R_0603_1608Metric
RS1, RS2, RS3, RS4, RS5, RS6, RS7, RS8, RS9, RS10, RS11, RS12, RS13: 510; R_0402_1005Metric
SW1: PAIR/BOOT; SW_SPST_TL3342
TP1: T14; TestPoint_Pad_D1.5mm
U1: ESP32-S3-MINI-1-N8; ESP32-S2-MINI-1
U2: ISC-SX1262-B; Ai-Thinker-Ra-01-LoRa

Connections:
+3V3: C1.1, C2.1, C3.1, C4.1, C5.1, J2.1, Q1.2 (S), R2.1, R3.1, R4.1, U1.3 (3V3), U2.3 (VDD)
/BOOT: J2.4, R3.2, SW1.1, U1.4 (IO0)
/DIV_LO: Q2.3 (D), R5.2
/EN: C6.1, J2.3, R2.2, U1.45 (EN)
/LED: R7.1, U1.34 (IO38)
/LED_A: D1.2 (A), R7.2
/LORA_BUSY: U1.22 (IO18), U2.10 (DIO4/BUSY)
/LORA_DIO1: U1.21 (IO17), U2.6 (DIO1)
/LORA_MISO: U1.38 (IO42), U2.13 (MISO)
/LORA_MOSI: U1.37 (IO41), U2.14 (MOSI)
/LORA_NSS: U1.35 (IO39), U2.15 (~NSS)
/LORA_RST: U1.25 (IO21), U2.4 (~RESET)
/LORA_SCK: U1.36 (IO40), U2.12 (SCK)
/P1: E1.1, RS1.2
/P2: E2.1, RS2.2
/P3: E3.1, RS3.2
/P4: E4.1, RS4.2
/P5: E5.1, RS5.2
/P6: E6.1, RS6.2
/P7: E7.1, RS7.2
/P8: E8.1, RS8.2
/P9: E9.1, RS9.2
/P10: E10.1, RS10.2
/P11: E11.1, RS11.2
/P12: E12.1, RS12.2
/Q1_G: Q1.1 (G), R1.1
/REF: E13.1, RS13.2
/RF_ANT: J1.1 (In), U2.1 (ANT)
/RXD0: J2.8, U1.40 (RXD0)
/T1: RS1.1, U1.5 (IO1)
/T2: RS2.1, U1.6 (IO2)
/T3: RS3.1, U1.7 (IO3)
/T4: RS4.1, U1.8 (IO4)
/T5: RS5.1, U1.9 (IO5)
/T6: RS6.1, U1.10 (IO6)
/T7: RS7.1, U1.11 (IO7)
/T8: RS8.1, U1.12 (IO8)
/T9: RS9.1, U1.13 (IO9)
/T10: RS10.1, U1.14 (IO10)
/T11: RS11.1, U1.15 (IO11)
/T12: RS12.1, U1.16 (IO12)
/T13: RS13.1, U1.17 (IO13)
/T14_SPARE: TP1.1, U1.18 (IO14)
/TXD0: J2.7, U1.39 (TXD0)
/USB_DN: J2.5, U1.23 (USB_D-)
/USB_DP: J2.6, U1.24 (USB_D+)
/VBAT_ADC: C7.1, R4.2, R5.1, U1.19 (IO15)
/VBAT_EN: Q2.1 (G), R6.1, U1.20 (IO16)
/VBAT_RAW: J3.1, Q1.3 (D)
GND: C1.2, C2.2, C3.2, C4.2, C5.2, C6.2, C7.2, D1.1 (K), E14.1, J1.2 (Ext), J2.2, J3.2, Q2.2 (S), R1.2, R6.2, SW1.2, U1.1 (GND), U1.2 (GND), U1.42 (GND), U1.43 (GND), U1.46 (GND), U1.47 (GND), U1.48 (GND), U1.49 (GND), U1.50 (GND), U1.51 (GND), U1.52 (GND), U1.53 (GND), U1.54 (GND), U1.55 (GND), U1.56 (GND), U1.57 (GND), U1.58 (GND), U1.59 (GND), U1.60 (GND), U1.61 (GND), U1.62 (GND), U1.63 (GND), U1.64 (GND), U1.65 (GND), U2.2 (GND), U2.9 (GND), U2.16 (GND)

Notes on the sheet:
Power: LiFePO4 14500 straight onto the 3V3 rail (3.0-3.4 V plateau, no regulator, ~0 uA quiescent). Q1 = reverse-polarity protection.
LoRa: ISC-SX1262-B in Ra-01 footprint - same module and pin map as WPC (BUSY = pad 10). SMA -> pigtail -> antenna on a 1.5 m pole above the canopy.
Battery sense: Q2 enables the 1M/1M divider only while sampling VBAT_ADC (ADC2, WiFi off).
Sensing strip: E1..E12 = 8x18 mm pads on 20 mm pitch (P1 = +7..+5 cm ... P12 = -15..-17 cm), E13 = dry reference, E14 = GND water-return pad.
Pads sit on F.Cu with NO mask opening; traces run on In2.Cu between In1 (hatched GND) and B.Cu (solid GND). Coat the whole strip.
RS1..RS13 = 510R touch series resistors, placed at the strip neck in the head.

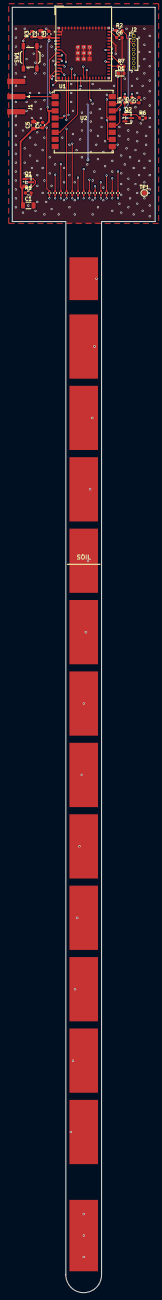
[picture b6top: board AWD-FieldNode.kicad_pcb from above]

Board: 4 copper layers, 40.0 x 360.0 mm, 51 parts (1 on the bottom side), 50 nets.

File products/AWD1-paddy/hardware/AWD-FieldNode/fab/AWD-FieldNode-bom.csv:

"Reference","Value","Footprint","QUANTITY"
"C1","47u","Capacitor_SMD:C_1206_3216Metric","1"
"C2,C5","10u","Capacitor_SMD:C_0805_2012Metric","2"
"C3,C4,C7","100n","Capacitor_SMD:C_0603_1608Metric","3"
"C6","1u","Capacitor_SMD:C_0603_1608Metric","1"
"D1","LED","LED_SMD:LED_0603_1608Metric","1"
"J1","SMA 866MHz","Connector_Coaxial:SMA_Amphenol_132289_EdgeMount","1"
"J2","PROG","Connector_PinHeader_1.27mm:PinHeader_1x08_P1.27mm_Vertical","1"
"J3","LiFePO4 14500","Connector_JST:JST_PH_S2B-PH-SM4-TB_1x02-1MP_P2.00mm_Horizontal","1"
"Q1","AO3401A","Package_TO_SOT_SMD:SOT-23","1"
"Q2","2N7002","Package_TO_SOT_SMD:SOT-23","1"
"R1,R6","100k","Resistor_SMD:R_0603_1608Metric","2"
"R2,R3","10k","Resistor_SMD:R_0603_1608Metric","2"
"R4,R5","1M","Resistor_SMD:R_0603_1608Metric","2"
"R7","1k","Resistor_SMD:R_0603_1608Metric","1"
"RS1-RS13","510","Resistor_SMD:R_0402_1005Metric","13"
"SW1","PAIR/BOOT","Button_Switch_SMD:SW_SPST_TL3342","1"
"U1","ESP32-S3-MINI-1-N8","RF_Module:ESP32-S2-MINI-1","1"
"U2","ISC-SX1262-B","RF_Module:Ai-Thinker-Ra-01-LoRa","1"

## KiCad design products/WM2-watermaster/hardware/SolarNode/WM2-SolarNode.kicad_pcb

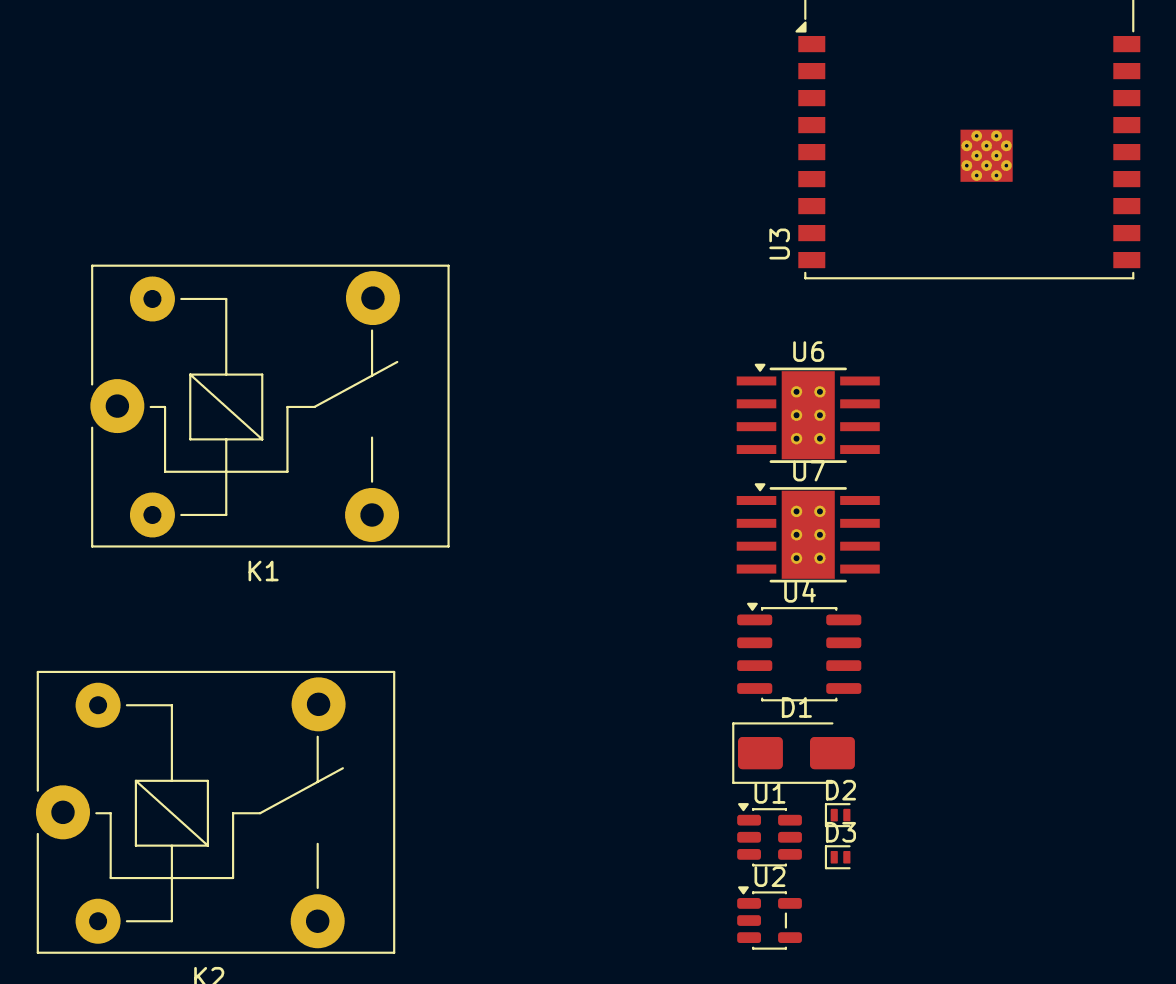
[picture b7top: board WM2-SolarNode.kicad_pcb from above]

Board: 2 copper layers, 11 parts (0 on the bottom side), 12 nets, no tracks yet.

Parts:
D1: SS34 (reverse-polarity); D_SMA
D2: PESD3V3U1UL (D-); D_SOD-882
D3: PESD3V3U1UL (D+); D_SOD-882
K1, K2: SRD-05VDC-SL-C; Relay_SPDT_SANYOU_SRD_Series_Form_C
U1: AP63205WU (fixed 5.0V out); TSOT-23-6
U2: AP2112K-3.3; SOT-23-5
U3: ESP32-C3-WROOM-02
U4: DS1307Z+; SOIC-8_3.9x4.9mm_P1.27mm
U6, U7: DRV8871DDA; Texas_HTSOP-8-1EP_3.9x4.9mm_P1.27mm_EP2.95x4.9mm_Mask2.4x3.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

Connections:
+3V3: U2.5 (VOUT), U3.1 (3V3), U4.8 (VCC)
+5V: K1.2, K2.2, U1.1 (FB), U2.1 (VIN), U2.3 (EN)
+12V: D1.1 (K), U1.2 (EN), U1.3 (IN), U6.5 (VM), U7.5 (VM)
/I2C_SCL: U3.8 (IO9), U4.6 (SCL)
/I2C_SDA: U3.7 (IO8), U4.5 (SDA)
/USB_DM: D2.2 (A), U3.13 (IO18)
/USB_DP: D3.2 (A), U3.14 (IO19)
/VALVE1_IN1: U3.10 (IO10), U6.3 (IN1)
/VALVE1_IN2: U3.11 (IO20/RXD), U6.2 (IN2)
/VALVE2_IN1: U3.12 (IO21/TXD), U7.3 (IN1)
/VALVE2_IN2: U3.16 (IO2), U7.2 (IN2)
GND: D2.1 (K), D3.1 (K), U1.4 (GND), U2.2 (GND), U3.9 (GND), U3.19 (GND), U4.4 (GND), U6.1 (GND), U6.7 (GND), U6.9 (GND), U7.1 (GND), U7.7 (GND), U7.9 (GND)
